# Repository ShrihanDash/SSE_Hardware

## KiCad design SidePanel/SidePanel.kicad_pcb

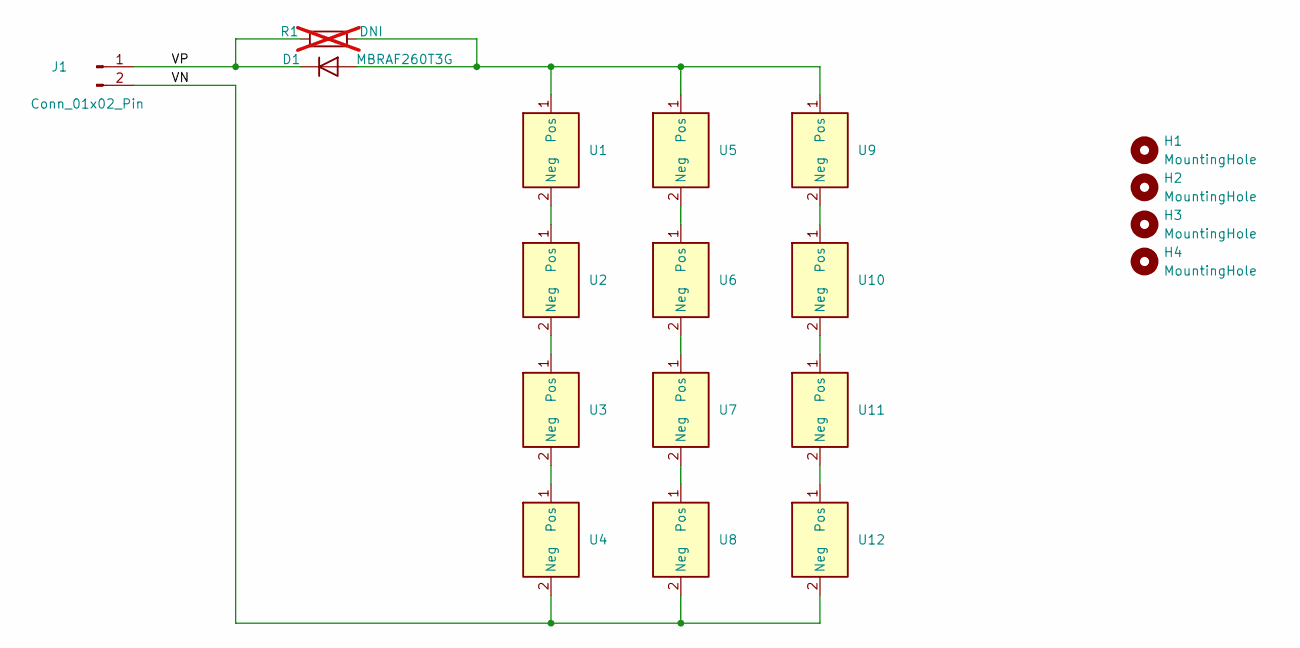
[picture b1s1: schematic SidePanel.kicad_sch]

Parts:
D1: MBRAF260T3G; D_SMA
H1, H2, H3, H4: MountingHole; MountingHole_3.2mm_M3_Pad_Via
J1: Conn_01x02_Pin; JST_PH_B2B-PH-SM4-TB_1x02-1MP_P2.00mm_Vertical
R1: DNI; R_1210_3225Metric; not fitted
U1, U2, U3, U4, U5, U6, U7, U8, U9, U10, U11, U12: solarBIT

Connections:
/VN: J1.2, U4.2 (Neg), U8.2 (Neg), U12.2 (Neg)
/VP: D1.1 (K), J1.1, R1.1
unnamed: D1.2 (A), R1.2, U1.1 (Pos), U5.1 (Pos), U9.1 (Pos)
unnamed: U1.2 (Neg), U2.1 (Pos)
unnamed: U2.2 (Neg), U3.1 (Pos)
unnamed: U3.2 (Neg), U4.1 (Pos)
unnamed: U5.2 (Neg), U6.1 (Pos)
unnamed: U6.2 (Neg), U7.1 (Pos)
unnamed: U7.2 (Neg), U8.1 (Pos)
unnamed: U10.2 (Neg), U11.1 (Pos)
unnamed: U9.2 (Neg), U10.1 (Pos)
unnamed: U11.2 (Neg), U12.1 (Pos)

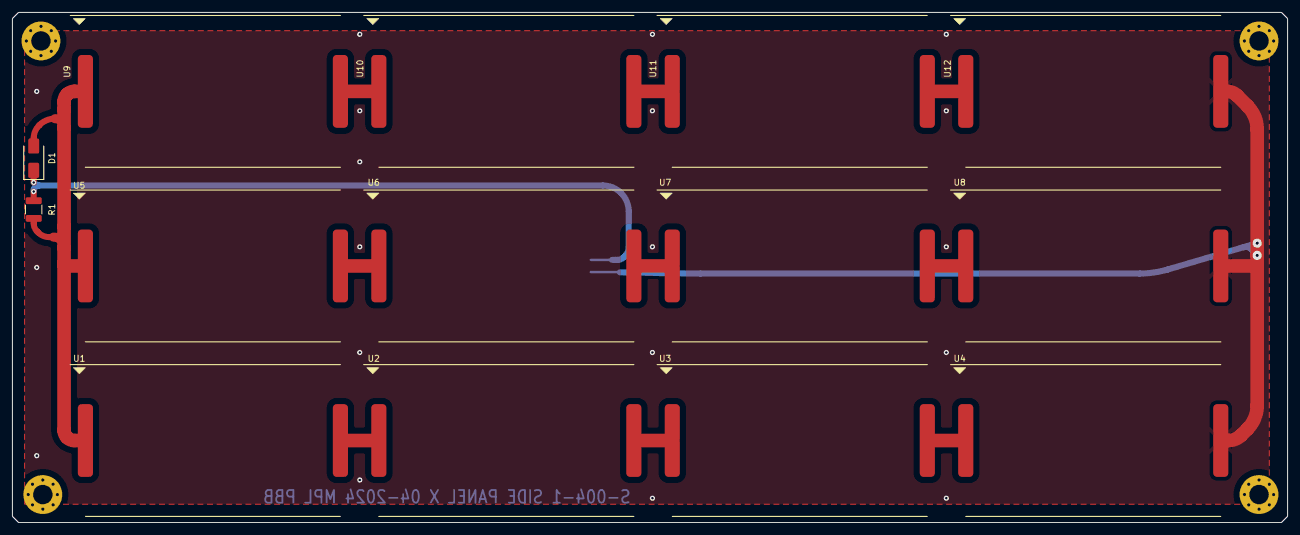
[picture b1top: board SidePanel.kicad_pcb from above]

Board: 2 copper layers, 210.0 x 84.0 mm, 19 parts (1 on the bottom side), 12 nets.

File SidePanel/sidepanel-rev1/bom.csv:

Designator,Footprint,Quantity,Value,LCSC Part #
D1,D_SMA,1,MBRAF260T3G,
J1,JST_PH_B2B-PH-SM4-TB_1x02-1MP_P2.00mm_Vertical,1,Conn_01x02_Pin,
R1,1210,1,DNI,
"U1, U10, U11, U12, U2, U3, U4, U5, U6, U7, U8, U9",solarBIT,12,~,

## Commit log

2024-02-29 SSE Hardware Files
2024-02-29 SSE_Hardware
2024-03-01 Added more fields to BOM.
2024-03-05 edits
2024-03-05 Improved Py-Cubed BOM
2024-04-04 Created Side Panel Circut
2024-04-06 SidePanel: approaching revision 1
    In conjunction with Porter, laid out first rev of side panel
2024-04-06 SidePanel Rev1
